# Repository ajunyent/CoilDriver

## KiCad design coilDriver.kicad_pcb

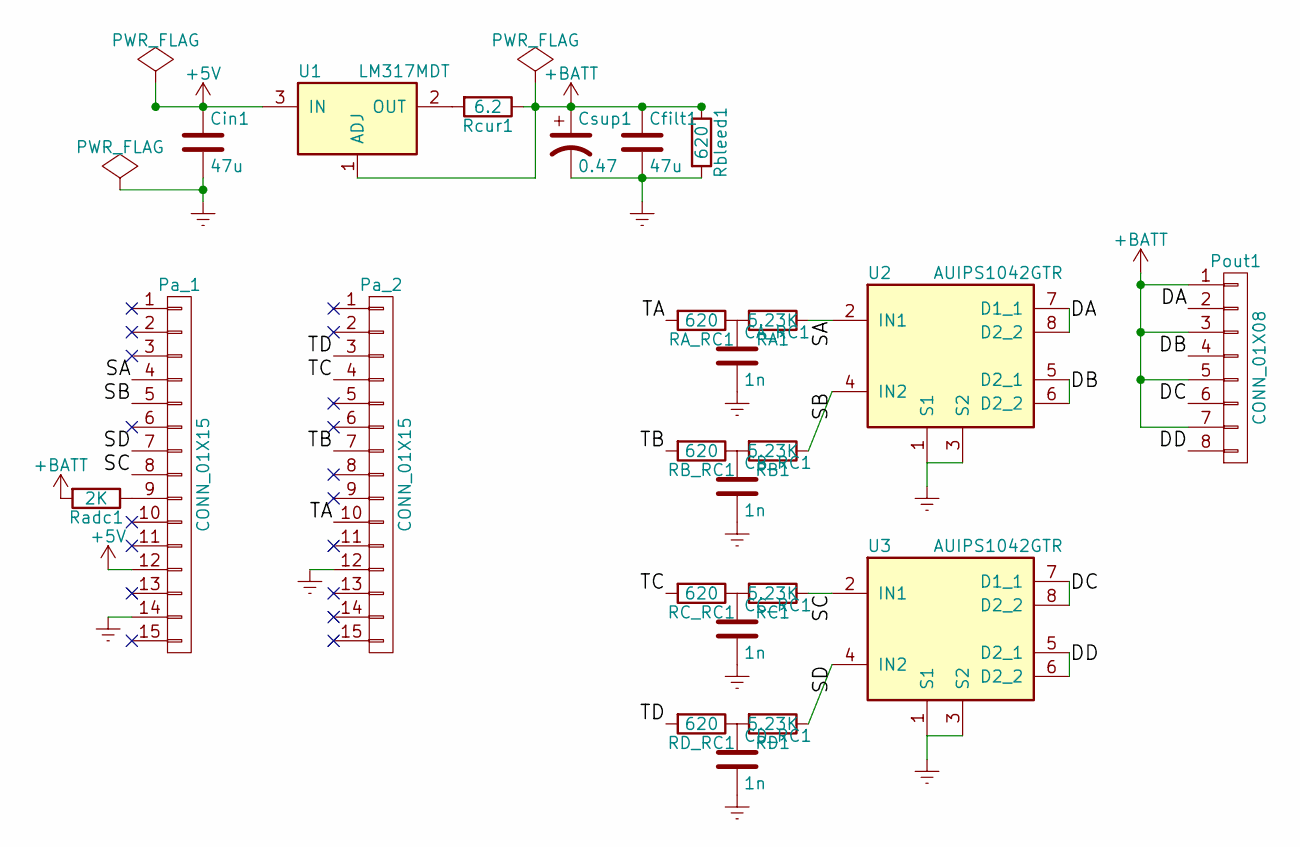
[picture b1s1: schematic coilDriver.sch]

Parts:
CA_RC1: 1n; C_0603
CB_RC1: 1n; C_0603
CC_RC1: 1n; C_0603
CD_RC1: 1n; C_0603
Cfilt1: 47u; C_0805_HandSoldering
Cin1: 47u; C_0805_HandSoldering
Csup1: 0.47; CP5
Pa_1, Pa_2: CONN_01X15; Pin_Header_Straight_1x15
Pout1: CONN_01X08; Pin_Header_Straight_1x08
RA1: 5.23K; R_0603
RA_RC1: 620; R_0603
RB1: 5.23K; R_0603
RB_RC1: 620; R_0603
RC1: 5.23K; R_0603
RC_RC1: 620; R_0603
RD1: 5.23K; R_0603
RD_RC1: 620; R_0603
Radc1: 2K; R_0603
Rbleed1: 620; R_0603
Rcur1: 6.2; R_2512_HandSoldering
U1: LM317MDT; TO-252-2Lead
U2, U3: AUIPS1042GTR; SOIC-8_3.9x4.9mm_Pitch1.27mm

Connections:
+5V: Cin1.1, Pa_1.12, U1.3 (IN)
+BATT: Cfilt1.1, Csup1.1, Pout1.1, Pout1.3, Pout1.5, Pout1.7, Radc1.2, Rbleed1.1, Rcur1.1, U1.1 (ADJ)
/DA: Pout1.2, U2.7 (D1_1), U2.8 (D2_2)
/DB: Pout1.4, U2.5 (D2_1), U2.6 (D2_2)
/DC: Pout1.6, U3.7 (D1_1), U3.8 (D2_2)
/DD: Pout1.8, U3.5 (D2_1), U3.6 (D2_2)
/SA: Pa_1.4, RA1.1, U2.2 (IN1)
/SB: Pa_1.5, RB1.1, U2.4 (IN2)
/SC: Pa_1.8, RC1.1, U3.2 (IN1)
/SD: Pa_1.7, RD1.1, U3.4 (IN2)
/TA: Pa_2.10, RA_RC1.2
/TB: Pa_2.7, RB_RC1.2
/TC: Pa_2.4, RC_RC1.2
/TD: Pa_2.3, RD_RC1.2
Earth: CA_RC1.2, CB_RC1.2, CC_RC1.2, CD_RC1.2, Cfilt1.2, Cin1.2, Csup1.2, Pa_1.14, Pa_2.12, Rbleed1.2, U2.1 (S1), U2.3 (S2), U3.1 (S1), U3.3 (S2)
unnamed: CA_RC1.1, RA1.2, RA_RC1.1
unnamed: CB_RC1.1, RB1.2, RB_RC1.1
unnamed: CC_RC1.1, RC1.2, RC_RC1.1
unnamed: CD_RC1.1, RD1.2, RD_RC1.1
unnamed: Pa_1.9, Radc1.1
unnamed: Rcur1.2, U1.2 (OUT)

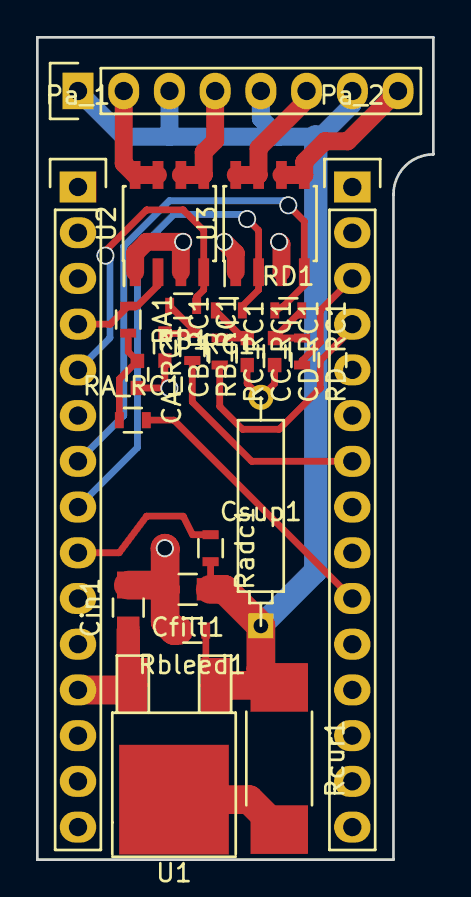
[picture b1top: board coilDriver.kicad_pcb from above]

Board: 2 copper layers, 22.0 x 45.7 mm, 24 parts (0 on the bottom side), 21 nets.

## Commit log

2018-08-06 First commit: Design files of the first prototype
